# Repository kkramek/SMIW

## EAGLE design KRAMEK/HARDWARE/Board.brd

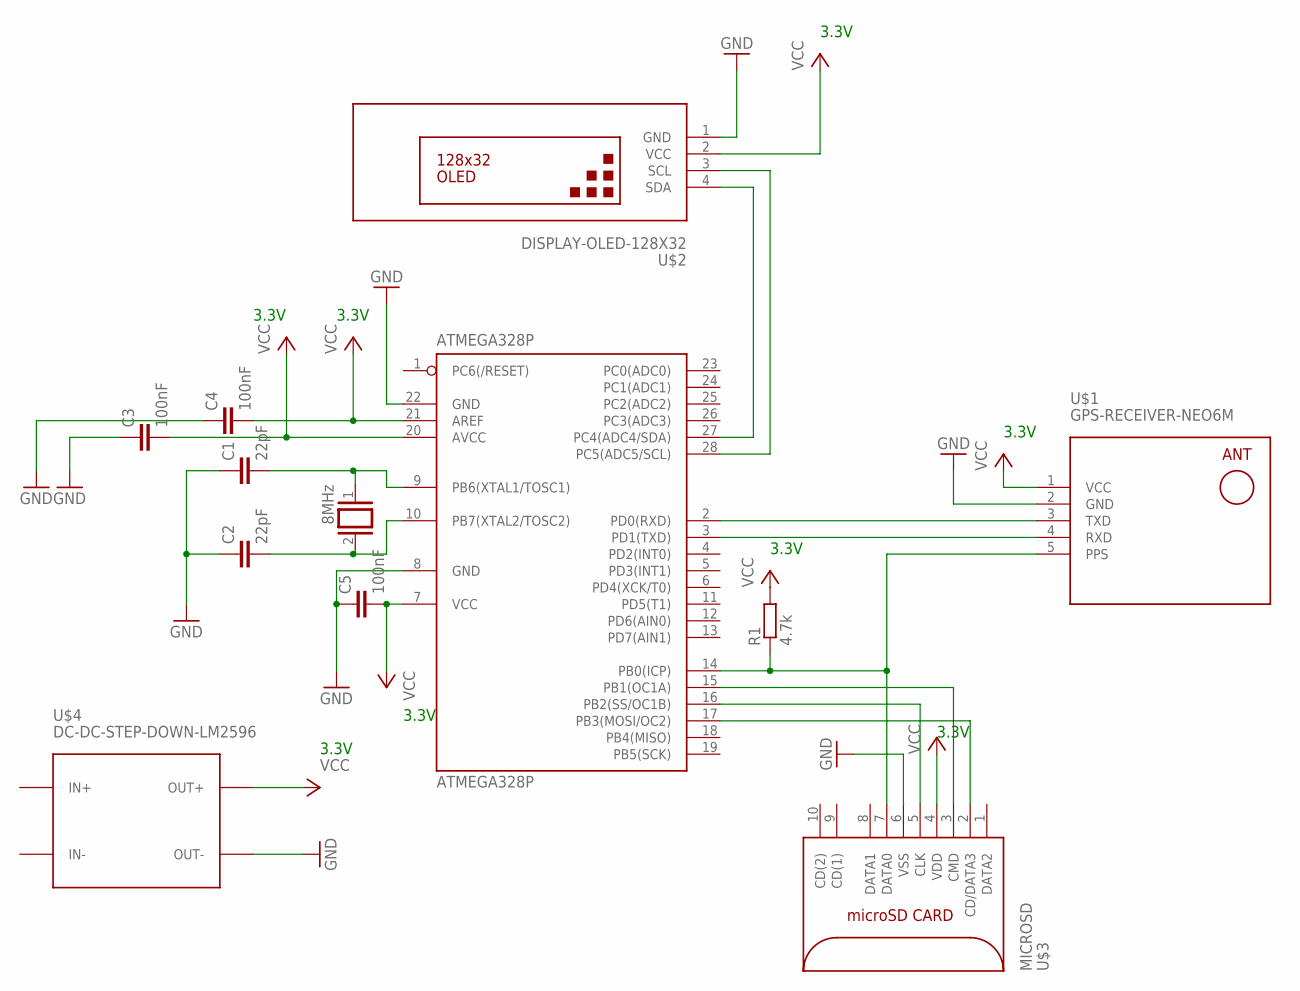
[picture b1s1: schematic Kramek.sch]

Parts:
ATMEGA328P: ATMEGA328P; DIL28-3
C1, C2: 22pF; C2.5-3
C3, C4, C5: 100nF; C2.5-3
Q1: 8MHz; Q
R1: 4.7k; 0204V
U$1: GPS-RECEIVER-NEO6M
U$2: DISPLAY-OLED-128X32
U$3: MICROSD; MICRO_SD_CONNECTOR
U$4: DC-DC-STEP-DOWN-LM2596

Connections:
GND: ATMEGA328P.8 (GND), ATMEGA328P.22 (GND), C1.1, C2.1, C5.1, U$1.2 (GND), U$2.1 (GND), U$3.6 (VSS), U$4.OUT-
unnamed: ATMEGA328P.2 (PD0(RXD)), U$1.3 (TXD)
unnamed: ATMEGA328P.3 (PD1(TXD)), U$1.4 (RXD)
unnamed: ATMEGA328P.14 (PB0(ICP)), R1.1, U$1.5 (PPS), U$3.7 (DATA0)
unnamed: ATMEGA328P.15 (PB1(OC1A)), U$3.3 (CMD)
unnamed: ATMEGA328P.16 (PB2(SS/OC1B)), U$3.5 (CLK)
unnamed: ATMEGA328P.17 (PB3(MOSI/OC2)), U$3.2 (CD/DATA3)
unnamed: ATMEGA328P.27 (PC4(ADC4/SDA)), U$2.4 (SDA)
unnamed: ATMEGA328P.28 (PC5(ADC5/SCL)), U$2.3 (SCL)
unnamed: ATMEGA328P.9 (PB6(XTAL1/TOSC1)), C1.2, Q1.1
unnamed: ATMEGA328P.10 (PB7(XTAL2/TOSC2)), C2.2, Q1.2
VCC: ATMEGA328P.7 (VCC), ATMEGA328P.20 (AVCC), ATMEGA328P.21 (AREF), C3.2, C4.2, C5.2, R1.2, U$1.1 (VCC), U$2.2 (VCC), U$3.4 (VDD), U$4.OUT+

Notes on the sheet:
3.3V

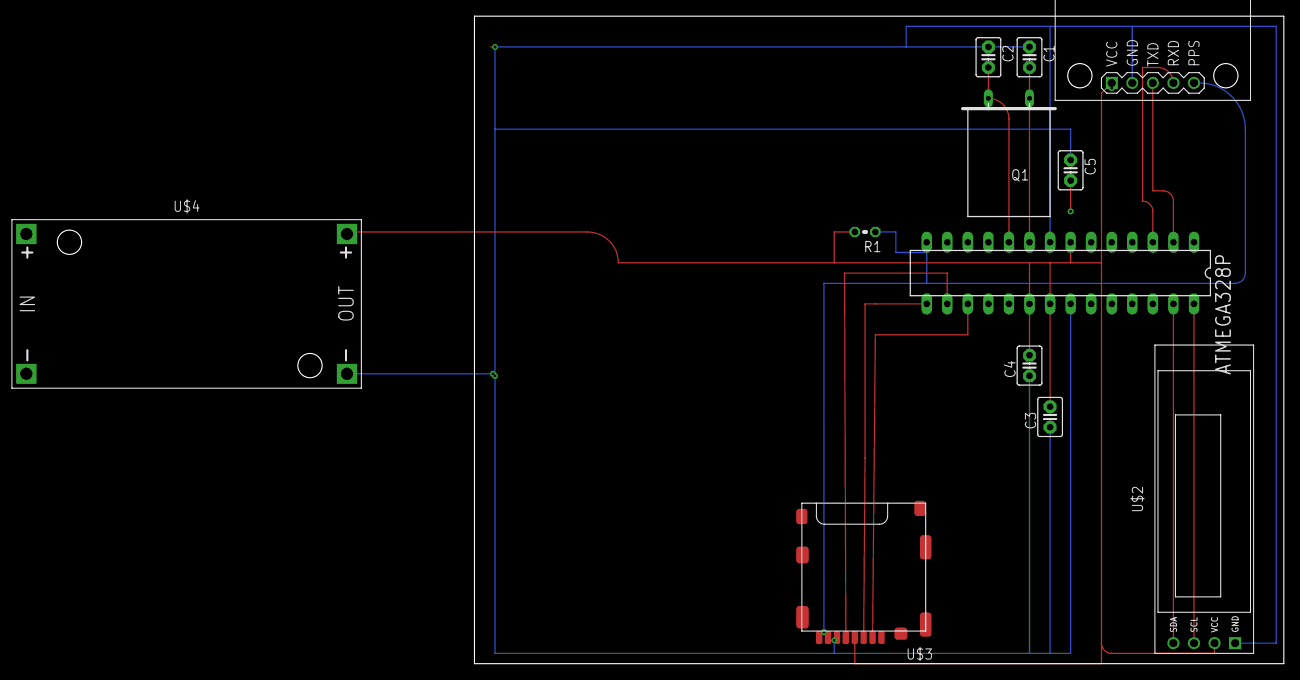
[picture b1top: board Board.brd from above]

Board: 2 copper layers, 100.0 x 80.0 mm, 12 parts (0 on the bottom side), 12 nets.

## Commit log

2019-09-08 Raport.pdf

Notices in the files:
parts and their libraries:
diy-modules: Released under the Creative Commons Attribution 4.0 International License: http://creativecommons.org/licenses/by/4.0
